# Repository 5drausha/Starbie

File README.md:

# Squarebie

This project is a modification of the Starbie starter project. Since I wanted to make something original, I decided to go down a slightly different path to Starbie. I wanted to turn this into more of a mini computer, desk assistant and macropad rather than a virtual pet.

Above is the picture of the 3d model (doesn't have the button caps in the model).

This is a picture of just the electronics.

This is the case.

And this is my PCB model.

My plan is to have this Squarbie be used as a sort of second mini device that pairs with my computer. I plan to have an app where you can do things such as set timers, reminders, make the 3 buttons on it customizable macropad keys, and display custom animations on it. But I'll have to leave that for later as I need the board in person (I don't know how to do it without it) to make the app. But for now, it functions as its own mini computer, with a stopwatch, a counter, and a reaction time game, which is still fully functional. Here is a picture of its simulated version:

This was a fun project and I learnt A LOT making this. I have never designed something in a CAD, so this was a great learning experience. Really looking forward to next week's project. :)

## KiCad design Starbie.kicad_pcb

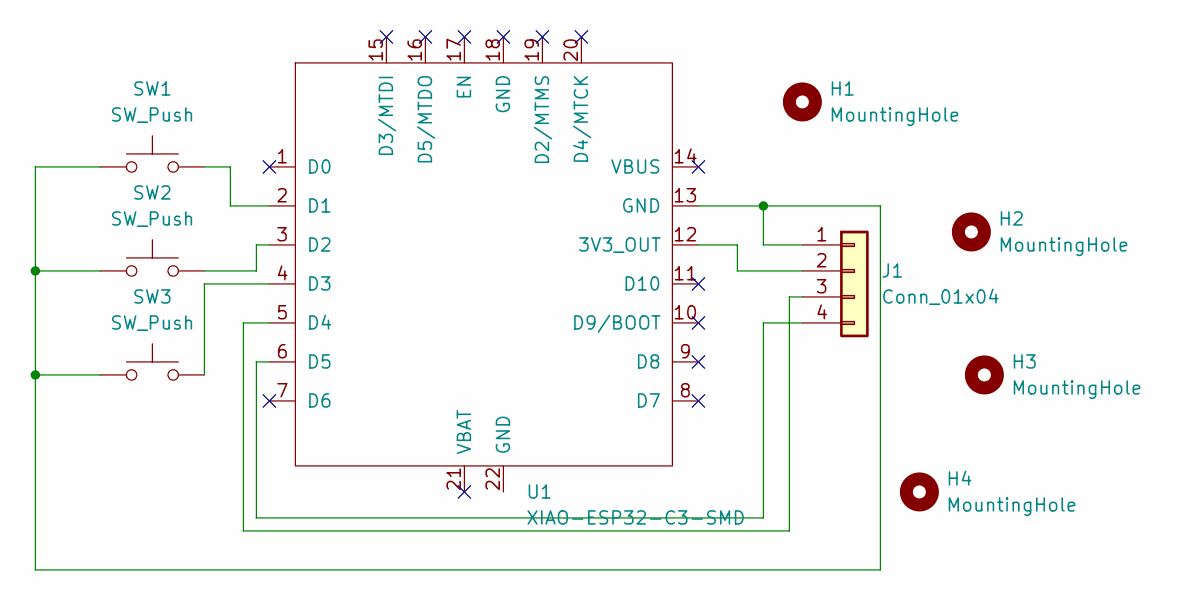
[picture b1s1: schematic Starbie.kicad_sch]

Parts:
H1, H2, H3, H4: MountingHole; MountingHole_3.2mm_M3
J1: Conn_01x04; Display_128x64_096_I2C
SW1, SW2, SW3: SW_Push; SW_PUSH-12mm
U1: XIAO-ESP32-C3-SMD; XIAO-ESP32-C6-DIP

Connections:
unnamed: J1.1, SW1.1, SW2.1, SW3.1, U1.13 (GND)
unnamed: J1.2, U1.12 (3V3_OUT)
unnamed: J1.3, U1.5 (D4)
unnamed: J1.4, U1.6 (D5)
unnamed: SW1.2, U1.2 (D1)
unnamed: SW2.2, U1.3 (D2)
unnamed: SW3.2, U1.4 (D3)

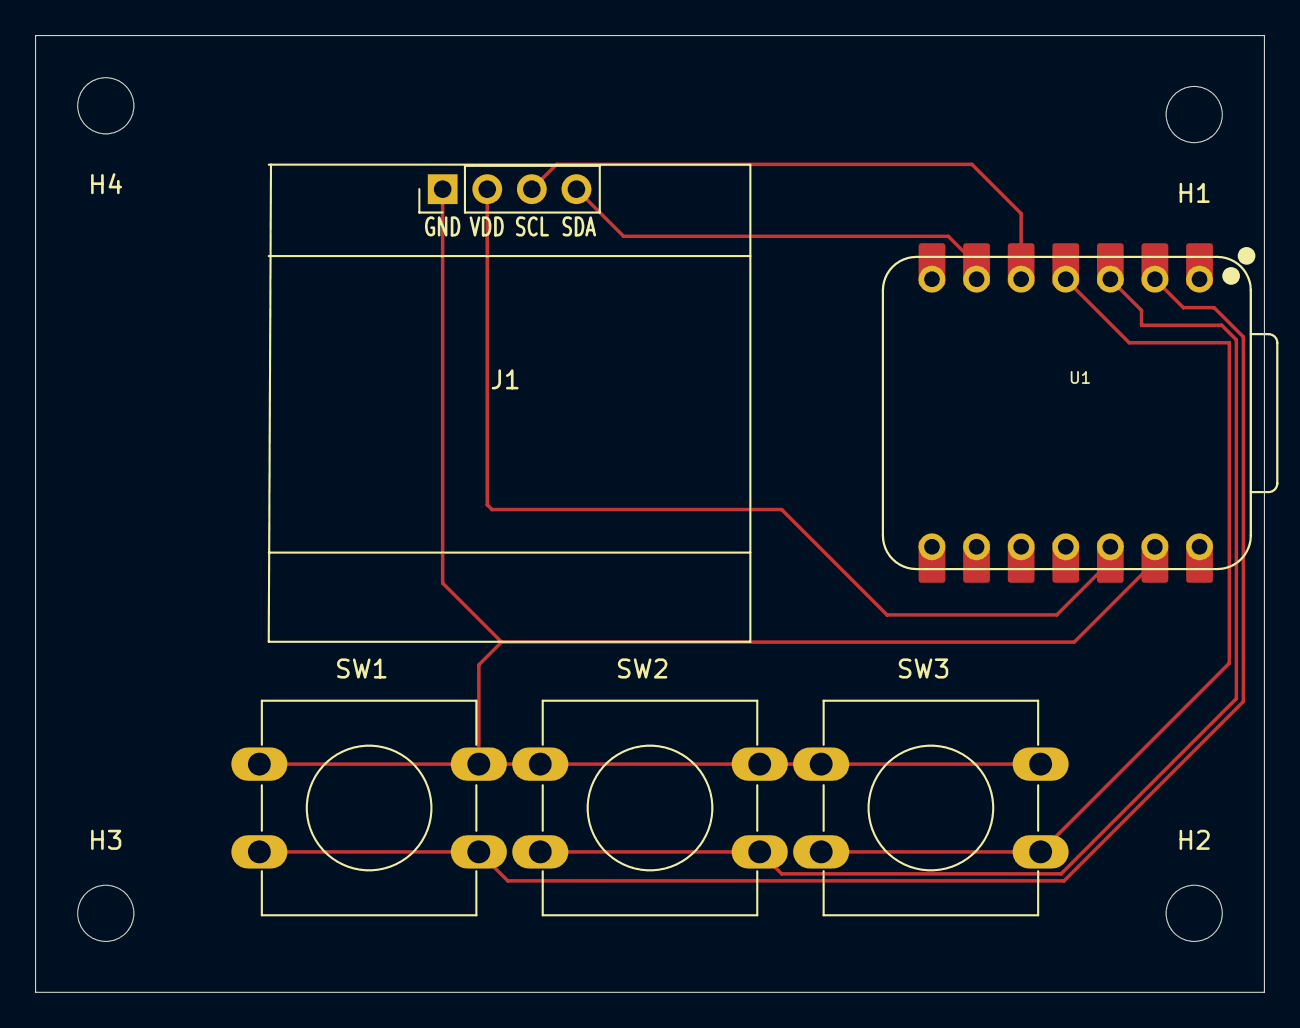
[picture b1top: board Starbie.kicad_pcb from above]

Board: 2 copper layers, 70.0 x 54.5 mm, 9 parts (0 on the bottom side), 7 nets.
